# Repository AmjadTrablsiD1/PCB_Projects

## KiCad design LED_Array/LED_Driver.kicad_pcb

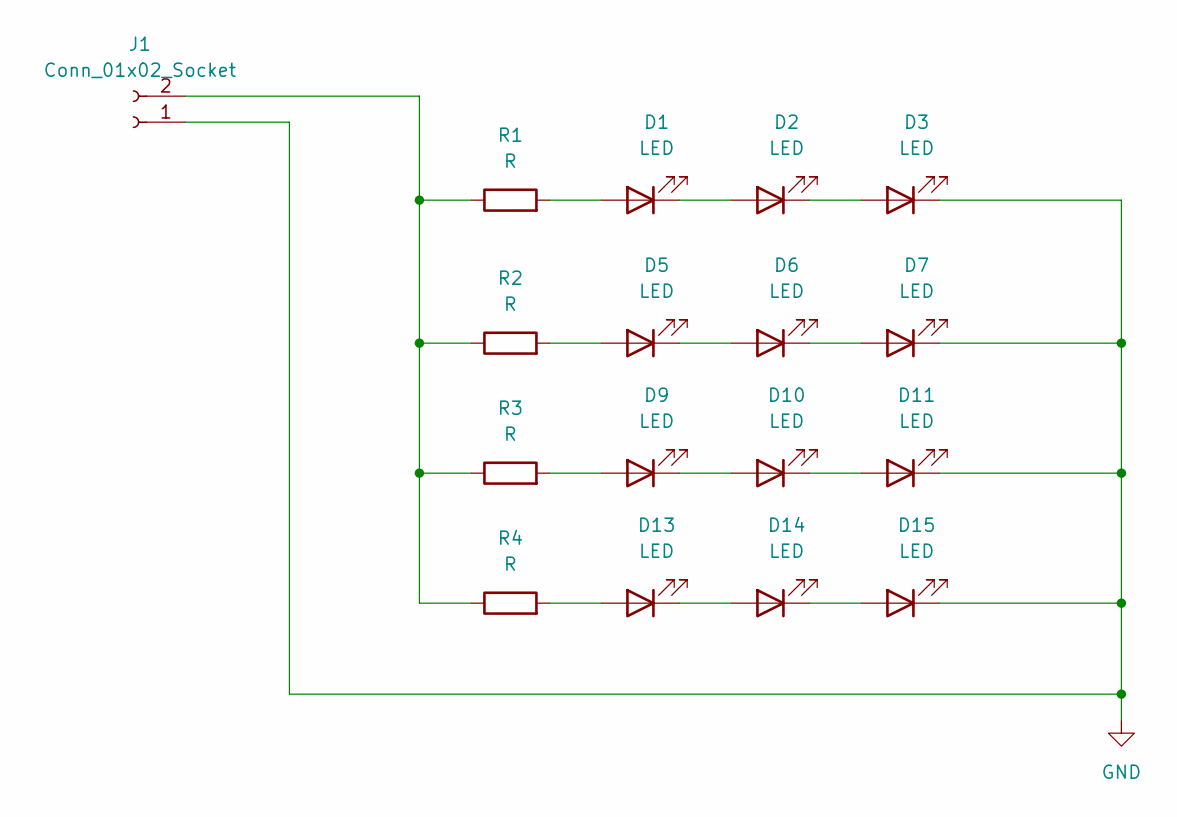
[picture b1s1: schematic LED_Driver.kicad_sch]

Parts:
D1, D2, D3, D5, D6, D7, D9, D10, D11, D13, D14, D15: LED; LED_1W_3W_R8
J1: Conn_01x02_Socket; PinSocket_1x02_P2.54mm_Vertical
R1, R2, R3, R4: R; R_1206_3216Metric_Pad1.30x1.75mm_HandSolder

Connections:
GND: D3.1 (K), D7.1 (K), D11.1 (K), D15.1 (K), J1.1
unnamed: D1.2 (A), R1.2
unnamed: D1.1 (K), D2.2 (A)
unnamed: D2.1 (K), D3.2 (A)
unnamed: D5.2 (A), R2.2
unnamed: D5.1 (K), D6.2 (A)
unnamed: D6.1 (K), D7.2 (A)
unnamed: D9.2 (A), R3.2
unnamed: D9.1 (K), D10.2 (A)
unnamed: D10.1 (K), D11.2 (A)
unnamed: D13.2 (A), R4.2
unnamed: D13.1 (K), D14.2 (A)
unnamed: D14.1 (K), D15.2 (A)
unnamed: J1.2, R1.1, R2.1, R3.1, R4.1

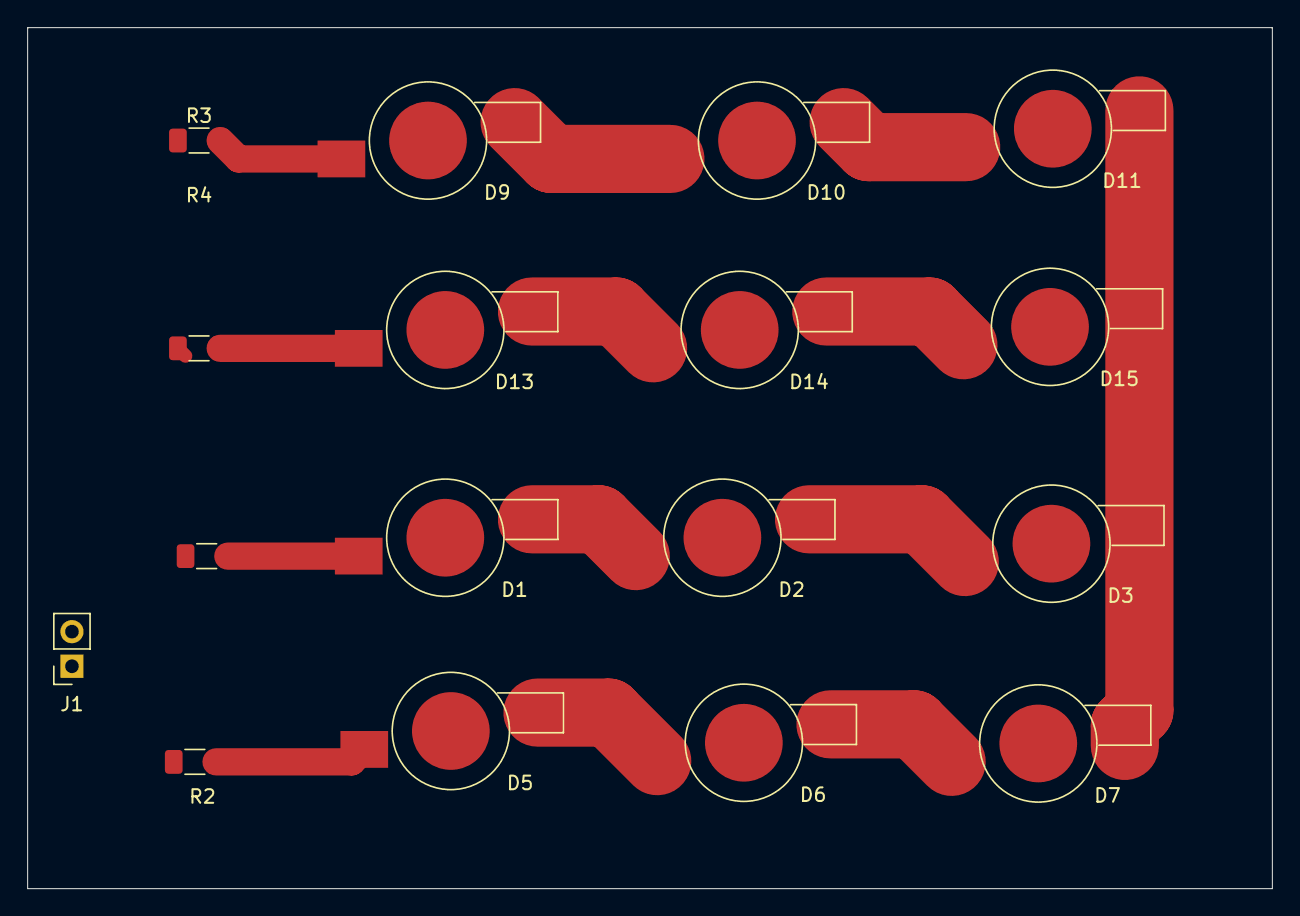
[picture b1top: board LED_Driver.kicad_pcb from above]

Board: 2 copper layers, 91.3 x 63.1 mm, 17 parts (0 on the bottom side), 14 nets.

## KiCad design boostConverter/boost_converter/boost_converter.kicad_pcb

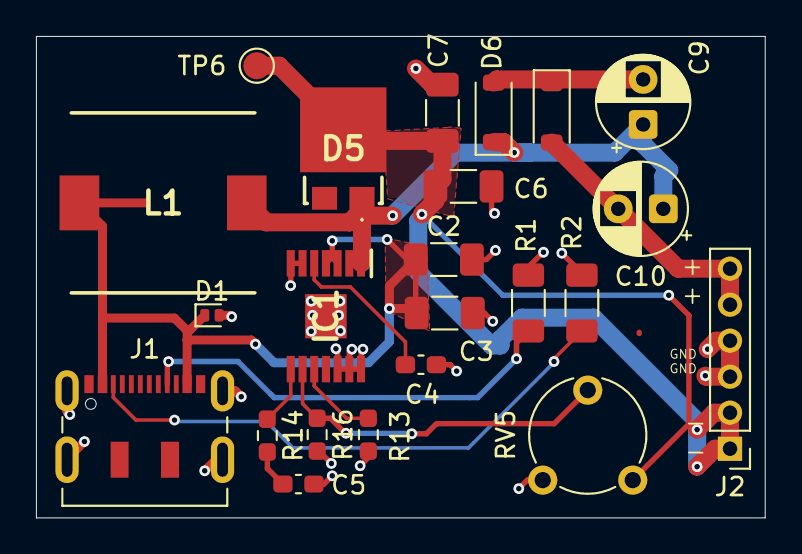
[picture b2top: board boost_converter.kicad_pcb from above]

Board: 4 copper layers, 40.5 x 26.7 mm, 23 parts (0 on the bottom side), 14 nets.

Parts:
C2, C3, C6, C7: 4u7; C_1206_3216Metric_Pad1.33x1.80mm_HandSolder
C4: 100n; C_0603_1608Metric_Pad1.08x0.95mm_HandSolder
C5: 1n; C_0603_1608Metric_Pad1.08x0.95mm_HandSolder
C9, C10: 100n; CP_Radial_D5.0mm_P2.50mm
D1: PESD5V0L1ULD; D_SOD-882D
D5: SS3P6L-E3_86A; SS3P6LE386A
D6, D7: MBR0520; D_SOD-123
IC1: TPS61175QPWPRQ1; SOP65P640X120-15N
J1: USB_C_Receptacle_PowerOnly_24P; USB_C_Receptacle_JAE_DX07S016JA1R1500
J2: Conn_01x06_Socket; PinHeader_1x06_P2.00mm_Vertical
L1: CDRH105RNP-220NC; INDPM102100X510N_Spule
R1, R2: 5k1; R_1206_3216Metric_Pad1.30x1.75mm_HandSolder
R13: 51k; R_0603_1608Metric_Pad0.98x0.95mm_HandSolder
R14: 1k; R_0603_1608Metric_Pad0.98x0.95mm_HandSolder
R16: 10K; R_0603_1608Metric_Pad0.98x0.95mm_HandSolder
RV5: R_Potentiometer; Potentiometer_Piher_PT-6-V_Vertical
TP6: TestPoint; TestPoint_Pad_D1.5mm

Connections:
5 V: C2.1, C3.1, D1.1 (K), IC1.3 (VIN), IC1.4 (EN), J1.A4 (VBUS), J1.A9 (VBUS), J1.B4 (VBUS), J1.B9 (VBUS), L1.1
25V: C6.1, C7.1, D5.3 (K), J2.1, J2.2, RV5.1, TP6.1
-25V: C10.2, D7.2 (A), J2.5, J2.6
GND: C2.2, C3.2, C4.2, C5.2, C6.2, C7.2, D1.2 (A), IC1.6 (SYNC), IC1.7 (AGND), IC1.12 (PGND_1), IC1.13 (PGND_2), IC1.14 (PGND_3), IC1.15 (EP), J2.3, J2.4, R1.2, R2.2, R13.2, R16.2, RV5.3
unnamed: C5.1, R14.2
unnamed: C9.1, C10.1, D5.1 (A_1), D6.1 (K), IC1.1 (SW_1), IC1.2 (SW_2), L1.2
unnamed: C9.2, D6.2 (A), D7.1 (K)
unnamed: IC1.8 (COMP), R14.1
unnamed: IC1.9 (FB), R16.1, RV5.2
unnamed: IC1.10 (FREQ), R13.1
unnamed: C4.1, IC1.5 (SS)
unnamed: J1.A5 (CC1), R2.1
unnamed: J1.B5 (CC2), R1.1
unnamed: J1.A1 (GND), J1.A12 (GND), J1.B1 (GND), J1.B12 (GND)

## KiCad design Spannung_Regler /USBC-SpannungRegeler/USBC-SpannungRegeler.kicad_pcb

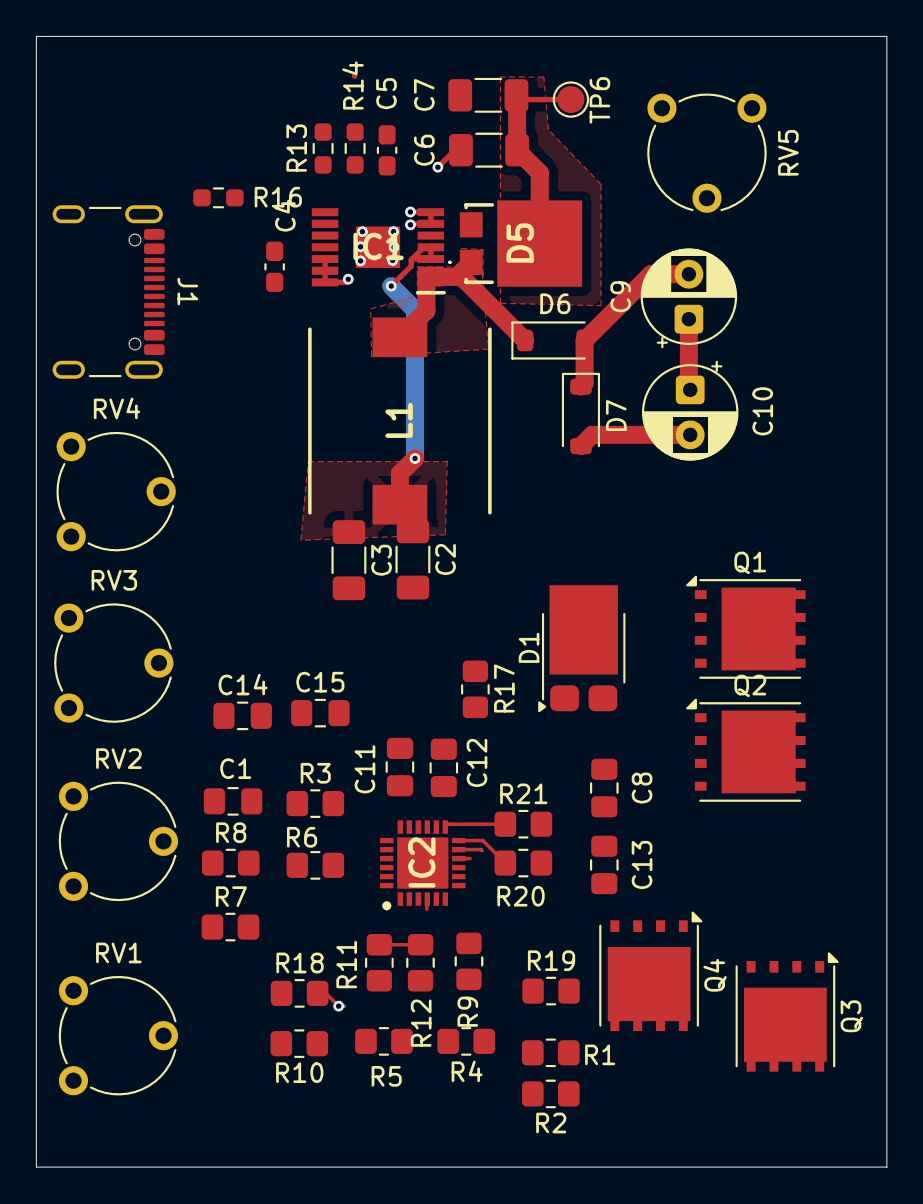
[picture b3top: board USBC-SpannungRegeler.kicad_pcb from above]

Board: 4 copper layers, 47.2 x 62.8 mm, 53 parts (0 on the bottom side), 31 nets.

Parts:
C1: 3u3; C_0805_2012Metric_Pad1.18x1.45mm_HandSolder
C2, C3, C6, C7: 4u7; C_1206_3216Metric_Pad1.33x1.80mm_HandSolder
C4: 100n; C_0603_1608Metric_Pad1.08x0.95mm_HandSolder
C5: 1n; C_0603_1608Metric_Pad1.08x0.95mm_HandSolder
C8, C11, C12, C13: 1u; C_0805_2012Metric_Pad1.18x1.45mm_HandSolder
C9, C10: 100n; CP_Radial_D5.0mm_P2.50mm
C14, C15: 0.1u; C_0805_2012Metric_Pad1.18x1.45mm_HandSolder
D1: PMEG030V050EPD; Nexperia_CFP15_SOT-1289
D5: SS3P6L-E3_86A; SS3P6LE386A
D6, D7: MBR0520; D_SOD-123
IC1: TPS61175QPWPRQ1; SOP65P640X120-15N
IC2: CYPD3177-24LQXQT
J1: USB4216-03-A; USB_C_Receptacle_GCT_USB4105-xx-A_16P_TopMnt_Horizontal
L1: CDRH105RNP-220NC; INDPM102100X510N_Spule
Q1, Q2, Q3, Q4: AON6411; AO_DFN-8-1EP_5.55x5.2mm_P1.27mm_EP4.12x4.6mm
R1, R2, R4, R5, R6, R7, R8, R11, R12, R18, R19: 1k; R_0805_2012Metric_Pad1.20x1.40mm_HandSolder
R3: 10k; R_0805_2012Metric_Pad1.20x1.40mm_HandSolder
R9: 4k7; R_0805_2012Metric_Pad1.20x1.40mm_HandSolder
R10, R17: 50k; R_0805_2012Metric_Pad1.20x1.40mm_HandSolder
R13: 51k; R_0603_1608Metric_Pad0.98x0.95mm_HandSolder
R14: 1k; R_0603_1608Metric_Pad0.98x0.95mm_HandSolder
R16: 10K; R_0603_1608Metric_Pad0.98x0.95mm_HandSolder
R20, R21: 2k2; R_0805_2012Metric_Pad1.20x1.40mm_HandSolder
RV1, RV2, RV3, RV4, RV5: R_Potentiometer; Potentiometer_Piher_PT-6-V_Vertical
TP6: TestPoint; TestPoint_Pad_D1.5mm

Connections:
5 V: C2.1, C3.1, IC1.3 (VIN), IC1.4 (EN), L1.1
25V: C6.1, C7.1, D5.3 (K), RV5.1, TP6.1
+3.3V: C12.1, C14.1, C15.1, IC2.23 (VDDD), R1.2, R4.2, R7.2, R9.1, R11.2, R20.2, R21.2, RV1.1, RV2.1, RV3.1, RV4.1
-25V: C10.2, D7.2 (A)
Coarse: IC2.5 (ISNK_COARSE), R1.1, R2.2, RV1.2
Fine: IC2.6 (ISNK_FINE), R4.1, R5.2, RV2.2
GND: C1.2, C2.2, C3.2, C4.2, C5.2, C6.2, C7.2, C11.2, C12.2, C14.2, C15.2, IC1.6 (SYNC), IC1.7 (AGND), IC1.12 (PGND_1), IC1.13 (PGND_2), IC1.14 (PGND_3), IC1.15 (EP), IC2.19 (GND_1), IC2.22 (GND_2), IC2.25 (EP), J1.A1 (GND_1), J1.B1 (GND_2), R2.1, R5.1, R8.1, R12.1, R13.2, R16.2, RV1.3, RV2.3, RV3.3, RV4.3, RV5.3
Max: IC2.2 (VBUS_MAX), R11.1, R12.2, RV3.2
Mini: IC2.1 (VBUS_MIN), R7.1, R8.2, RV4.2
unnamed: C5.1, R14.2
unnamed: D1.3 (K), Q1.1 (S), Q1.2 (S), Q1.3 (S), Q4.1 (S), Q4.2 (S), Q4.3 (S), R17.1
unnamed: C9.1, C10.1, D5.1 (A_1), D6.1 (K), IC1.1 (SW_1), IC1.2 (SW_2), L1.2
unnamed: C9.2, D6.2 (A), D7.1 (K)
unnamed: IC1.8 (COMP), R14.1
unnamed: IC1.9 (FB), R16.1, RV5.2
unnamed: IC1.10 (FREQ), R13.1
unnamed: C4.1, IC1.5 (SS)
unnamed: IC2.15 (CC1), J1.B5 (CC2)
unnamed: IC2.14 (CC2), J1.A5 (CC1)
unnamed: IC2.9 (FAULT), R19.1
unnamed: IC2.10 (FLIP), R9.2
unnamed: IC2.4 (SAFE_PWR_EN), R18.2
unnamed: IC2.3 (VBUS_FET_EN), R6.2
unnamed: C1.1, C8.1, IC2.18 (VBUS_IN), J1.A4 (VBUS_1), J1.B4 (VBUS_2), Q1.5 (D), Q2.5 (D), R3.1, R10.1
unnamed: C11.1, IC2.24 (VCCD)
unnamed: C8.2, C13.2, D1.1 (A), D1.2 (A), Q1.4 (G), Q4.4 (G), R3.2, R6.1, R17.2
unnamed: Q2.4 (G), Q3.4 (G), R10.2, R18.1
unnamed: Q2.1 (S), Q2.2 (S), Q2.3 (S), Q3.1 (S), Q3.2 (S), Q3.3 (S)
SCL: IC2.13 (HPI_SCL), R21.1
SDA: IC2.12 (HPI_SDA), R20.1
V_out: C13.1, IC2.11 (VDC_OUT), Q4.5 (D)

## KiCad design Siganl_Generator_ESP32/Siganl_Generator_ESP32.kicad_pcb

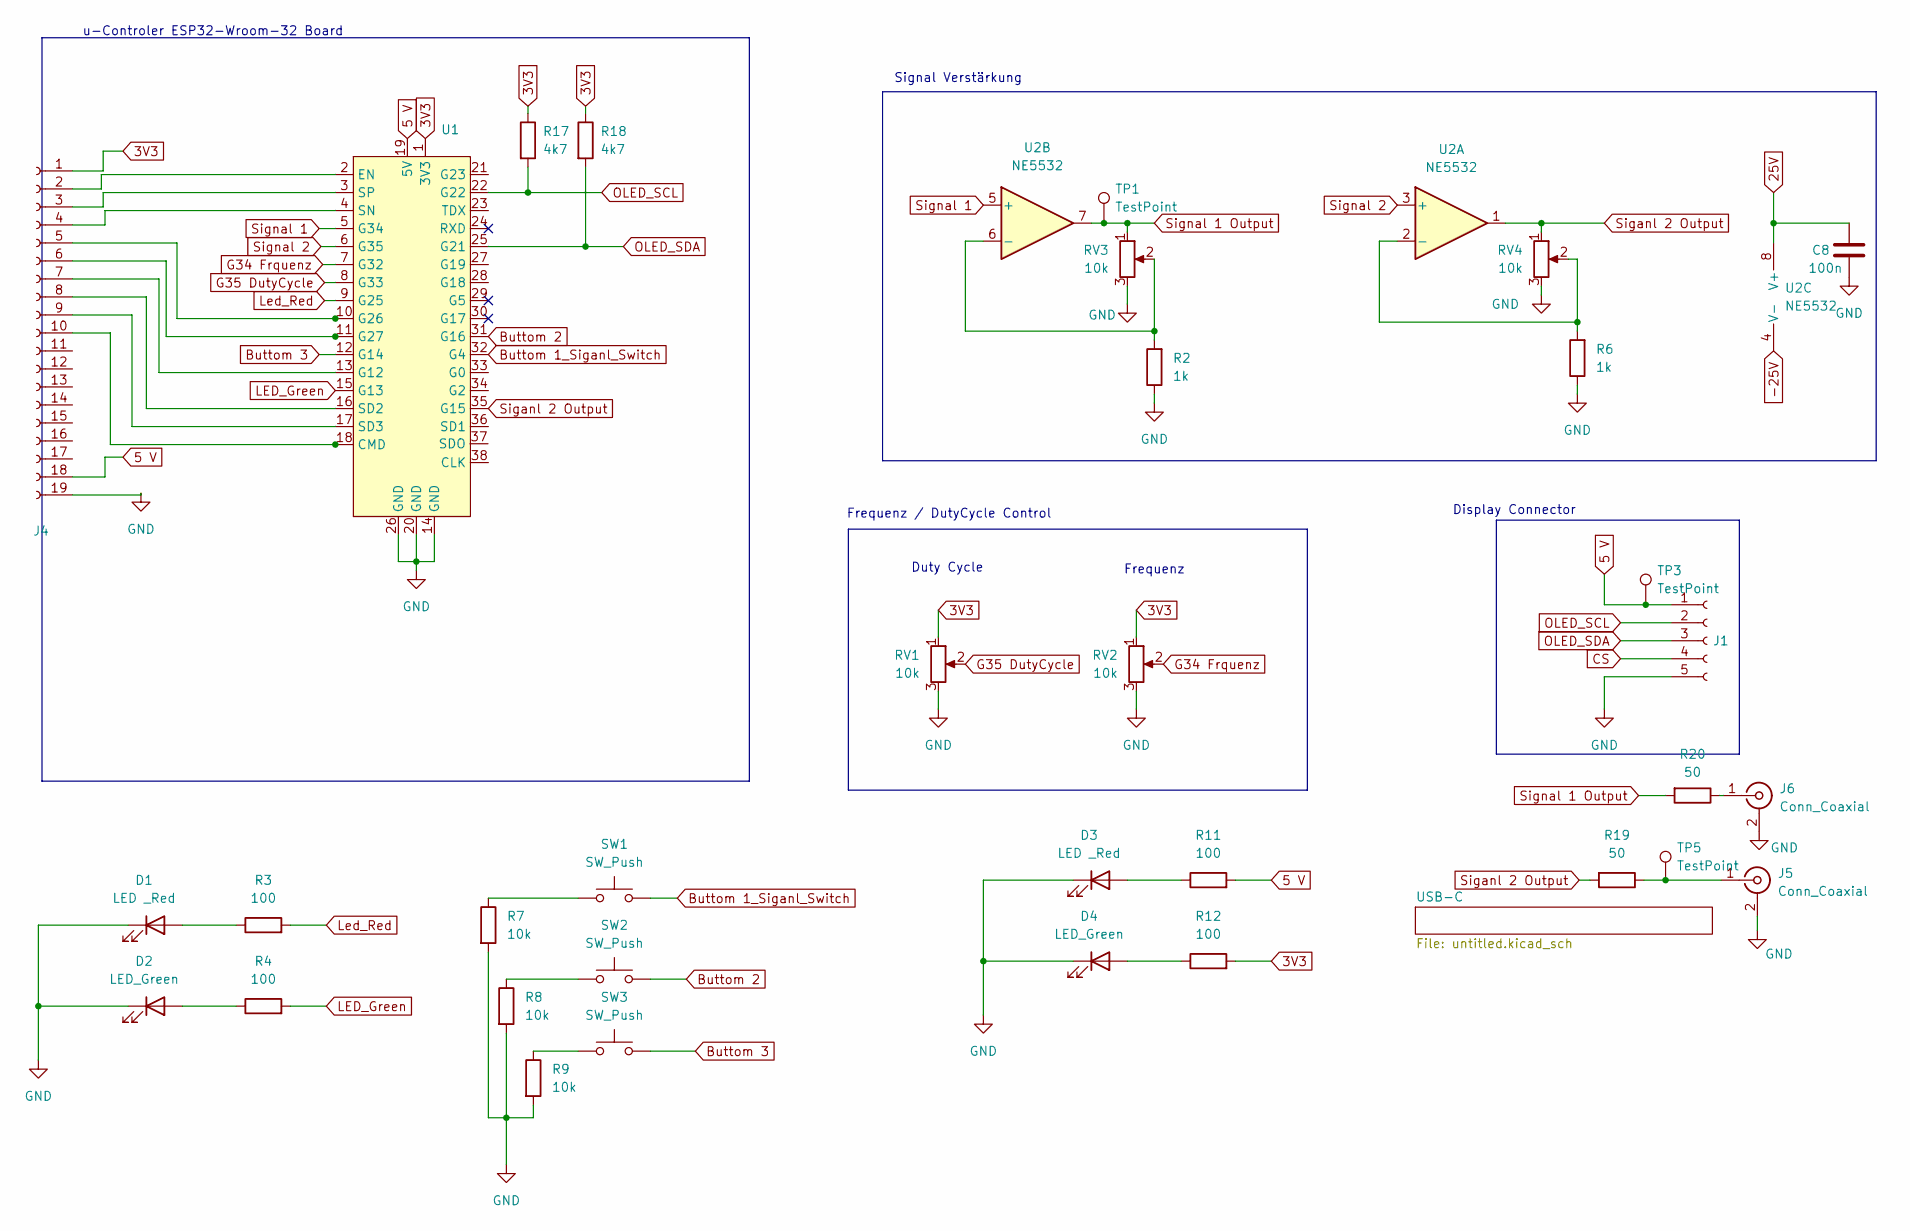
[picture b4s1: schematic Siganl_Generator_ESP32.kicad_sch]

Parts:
C8: 100n; C_0603_1608Metric_Pad1.08x0.95mm_HandSolder
D1, D3: LED _Red; D_1206_3216Metric
D2, D4: LED_Green; D_1206_3216Metric
J1: Conn_01x05_Socket; PinSocket_1x05_P2.54mm_Vertical
J4: Conn_01x19_Socket; PinSocket_1x19_P2.54mm_Vertical
J5, J6: Conn_Coaxial; SMA_Amphenol_132289_EdgeMount
R2, R6: 1k; R_0603_1608Metric_Pad0.98x0.95mm_HandSolder
R3, R4, R11, R12: 100; R_0603_1608Metric_Pad0.98x0.95mm_HandSolder
R7, R8, R9: 10k; R_0603_1608Metric_Pad0.98x0.95mm_HandSolder
R17, R18: 4k7; R_0603_1608Metric_Pad0.98x0.95mm_HandSolder
R19, R20: 50; R_0603_1608Metric_Pad0.98x0.95mm_HandSolder
RV1, RV2, RV3, RV4: 10k; Potentiometer_Alps_RK163_Single_Horizontal
SW1, SW2, SW3: SW_Push; SW_PUSH-12mm
TP1, TP3: TestPoint; TestPoint_Pad_D1.0mm
TP5: TestPoint; TestPoint_Pad_D1.5mm
U1: ESP_32_socket
U2: NE5532; DIP-8_W7.62mm

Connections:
3V3: J4.1, R12.2, R17.1, R18.1, RV1.1, RV2.1, U1.1 (3V3)
5 V: J1.1, J4.18, R11.2, TP3.1, U1.19 (5V); also elsewhere on the board
25V: C8.1, U2.8 (V+); also elsewhere on the board
-25V: U2.4 (V-); also elsewhere on the board
Buttom 1_Siganl_Switch: SW1.2, U1.32 (G4)
Buttom 2: SW2.2, U1.31 (G16)
Buttom 3: SW3.2, U1.12 (G14)
CS: J1.4
G34 Frquenz: RV2.2, U1.7 (G32)
G35 DutyCycle: RV1.2, U1.8 (G33)
GND: C8.2, D1.1 (K), D2.1 (K), D3.1 (K), D4.1 (K), J1.5, J4.19, J5.2 (Ext), J6.2 (Ext), R2.1, R6.1, R7.2, R8.2, R9.2, RV1.3, RV2.3, RV3.3, RV4.3, U1.14 (GND), U1.20 (GND), U1.26 (GND); also elsewhere on the board
LED_Green: R4.2, U1.15 (G13)
Led_Red: R3.2, U1.9 (G25)
unnamed: D1.2 (A), R3.1
unnamed: D2.2 (A), R4.1
unnamed: D3.2 (A), R11.1
unnamed: D4.2 (A), R12.1
unnamed: J4.2, U1.2 (EN)
unnamed: J4.3, U1.3 (SP)
unnamed: J4.4, U1.4 (SN)
unnamed: J4.5, U1.10 (G26)
unnamed: J4.6, U1.11 (G27)
unnamed: J4.7, U1.13 (G12)
unnamed: J4.8, U1.16 (SD2)
unnamed: J4.9, U1.17 (SD3)
unnamed: J4.10, U1.18 (CMD)
unnamed: J5.1 (In), R19.1, TP5.1
unnamed: J6.1 (In), R20.1
unnamed: R7.1, SW1.1
unnamed: R8.1, SW2.1
unnamed: R9.1, SW3.1
unnamed: R6.2, RV4.2, U2.2 (-)
unnamed: R2.2, RV3.2, U2.6 (-)
OLED_SCL: J1.2, R17.2, U1.22 (G22)
OLED_SDA: J1.3, R18.2, U1.25 (G21)
Siganl 2 Output: R19.2, RV4.1, U1.35 (G15), U2.1
Signal 1: U1.5 (G34), U2.5 (+)
Signal 1 Output: R20.2, RV3.1, TP1.1, U2.7
Signal 2: U1.6 (G35), U2.3 (+)

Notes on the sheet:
u-Controler ESP32-Wroom-32 Board
Signal Verstärkung
Frequenz / DutyCycle Control
Display Connector
Frequenz
Duty Cycle

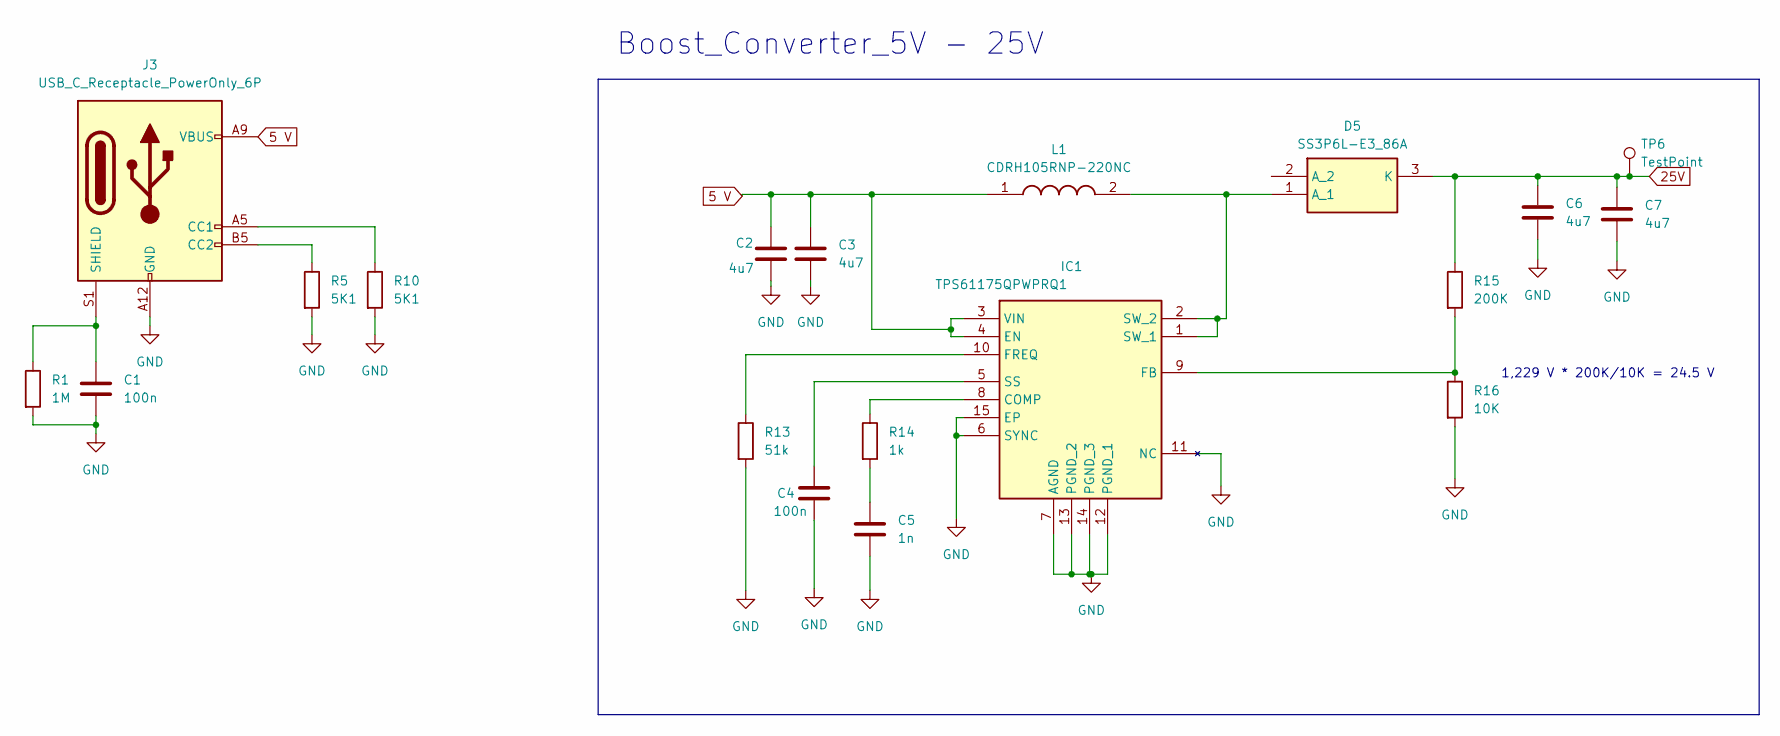
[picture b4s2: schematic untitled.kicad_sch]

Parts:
C1: 100n; C_1206_3216Metric
C2, C3, C6, C7: 4u7; C_1206_3216Metric_Pad1.33x1.80mm_HandSolder
C4: 100n; C_0603_1608Metric_Pad1.08x0.95mm_HandSolder
C5: 1n; C_0603_1608Metric_Pad1.08x0.95mm_HandSolder
D5: SS3P6L-E3_86A; SS3P6LE386A; Manufacturer_Part_Number SS3P6L-E3/86A
IC1: TPS61175QPWPRQ1; SOP65P640X120-15N; Mouser Part Number 595-TPS61175QPWPRQ1
J3: USB_C_Receptacle_PowerOnly_6P; USB_C_Receptacle_GCT_USB4125-xx-x-0190_6P_TopMnt_Horizontal
L1: CDRH105RNP-220NC; INDPM102100X510N_Spule; Mouser Part Number 851-CDRH105RNP-220NC
R1: 1M; R_1206_3216Metric
R5, R10: 5K1; R_0603_1608Metric_Pad0.98x0.95mm_HandSolder
R13: 51k; R_0603_1608Metric_Pad0.98x0.95mm_HandSolder
R14: 1k; R_0603_1608Metric_Pad0.98x0.95mm_HandSolder
R15: 200K; R_0603_1608Metric_Pad0.98x0.95mm_HandSolder
R16: 10K; R_0603_1608Metric_Pad0.98x0.95mm_HandSolder
TP6: TestPoint; TestPoint_Pad_D1.5mm

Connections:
5 V: C2.1, C3.1, IC1.3 (VIN), IC1.4 (EN), J3.A9 (VBUS), J3.B9 (VBUS), L1.1; also elsewhere on the board
25V: C6.1, C7.1, D5.3 (K), R15.1, TP6.1; also elsewhere on the board
GND: C1.2, C2.2, C3.2, C4.2, C5.2, C6.2, C7.2, IC1.6 (SYNC), IC1.7 (AGND), IC1.11 (NC), IC1.12 (PGND_1), IC1.13 (PGND_2), IC1.14 (PGND_3), IC1.15 (EP), J3.A12 (GND), J3.B12 (GND), R1.2, R5.2, R10.2, R13.2, R16.2; also elsewhere on the board
unnamed: C5.1, R14.2
unnamed 18: D5.1 (A_1), IC1.1 (SW_1), IC1.2 (SW_2), L1.2; also elsewhere on the board
unnamed: IC1.8 (COMP), R14.1
unnamed: IC1.9 (FB), R15.2, R16.1
unnamed: IC1.10 (FREQ), R13.1
unnamed: C4.1, IC1.5 (SS)
unnamed: J3.A5 (CC1), R10.1
unnamed: J3.B5 (CC2), R5.1
unnamed: C1.1, J3.S1 (SHIELD), R1.1

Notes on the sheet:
1,229 V * 200K/10K = 24.5 V
Boost_Converter_5V - 25V

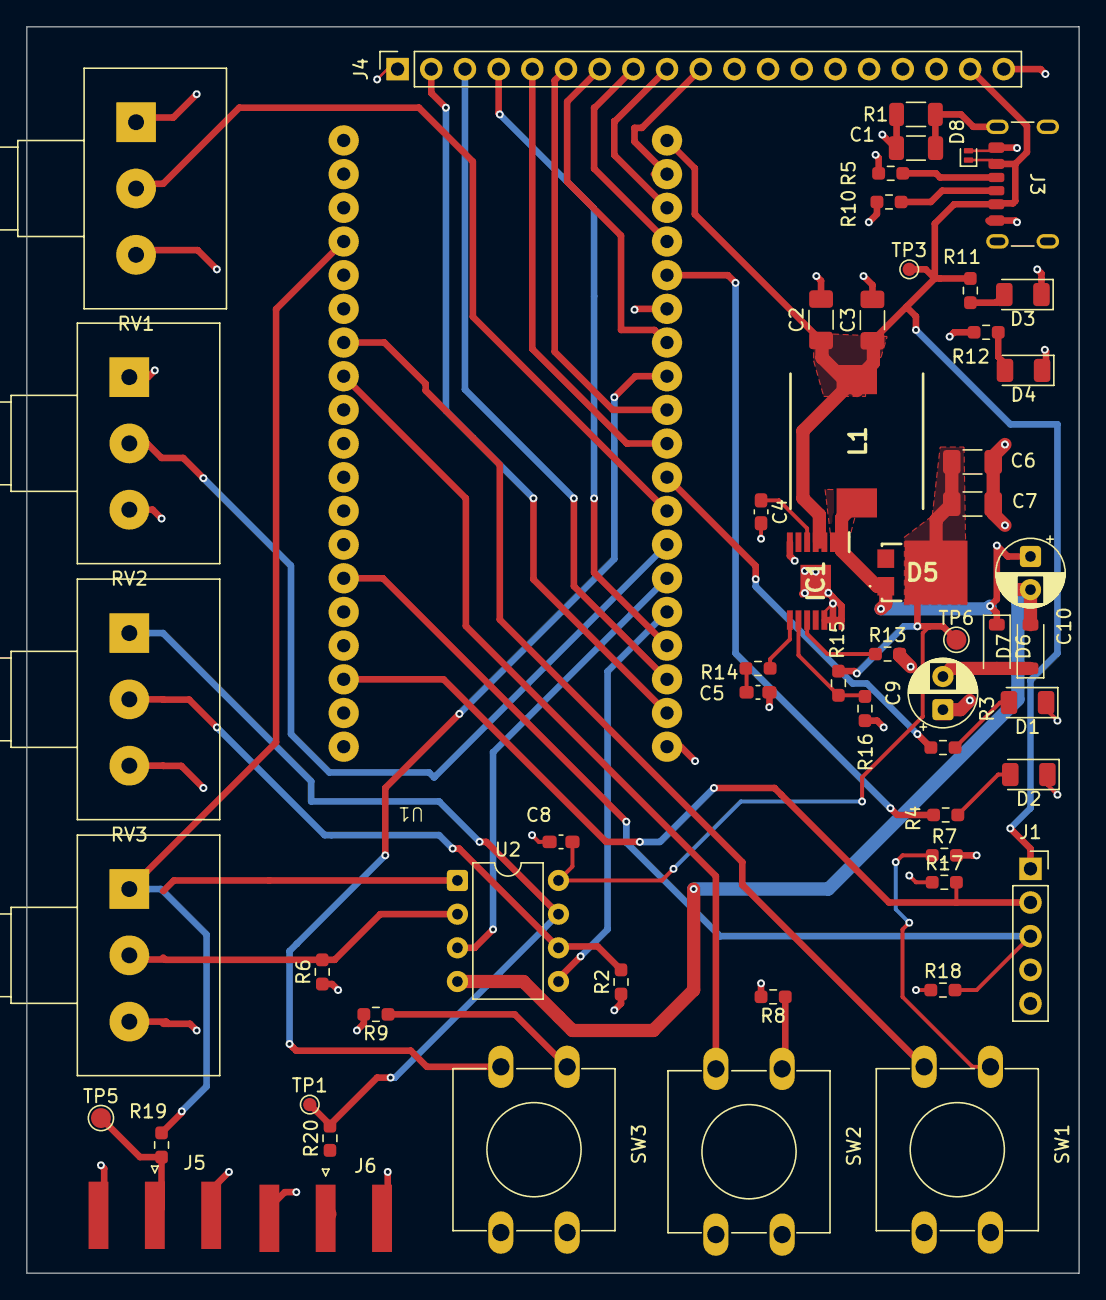
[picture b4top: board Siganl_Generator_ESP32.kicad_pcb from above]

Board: 4 copper layers, 79.4 x 94.0 mm, 58 parts (0 on the bottom side), 48 nets.

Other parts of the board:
C9, C10: 100n; CP_Radial_D5.0mm_P2.50mm
D6, D7: MBR0520; D_SOD-123
D8: PESD5V0L1UL; D_SOD-882

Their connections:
5 V: D8.1 (K); also elsewhere on the board
-25V: C10.2, D7.2 (A); also elsewhere on the board
GND: D8.2 (A); also elsewhere on the board
unnamed 18: C9.1, C10.1, D6.1 (K); also elsewhere on the board
unnamed: C9.2, D6.2 (A), D7.1 (K)

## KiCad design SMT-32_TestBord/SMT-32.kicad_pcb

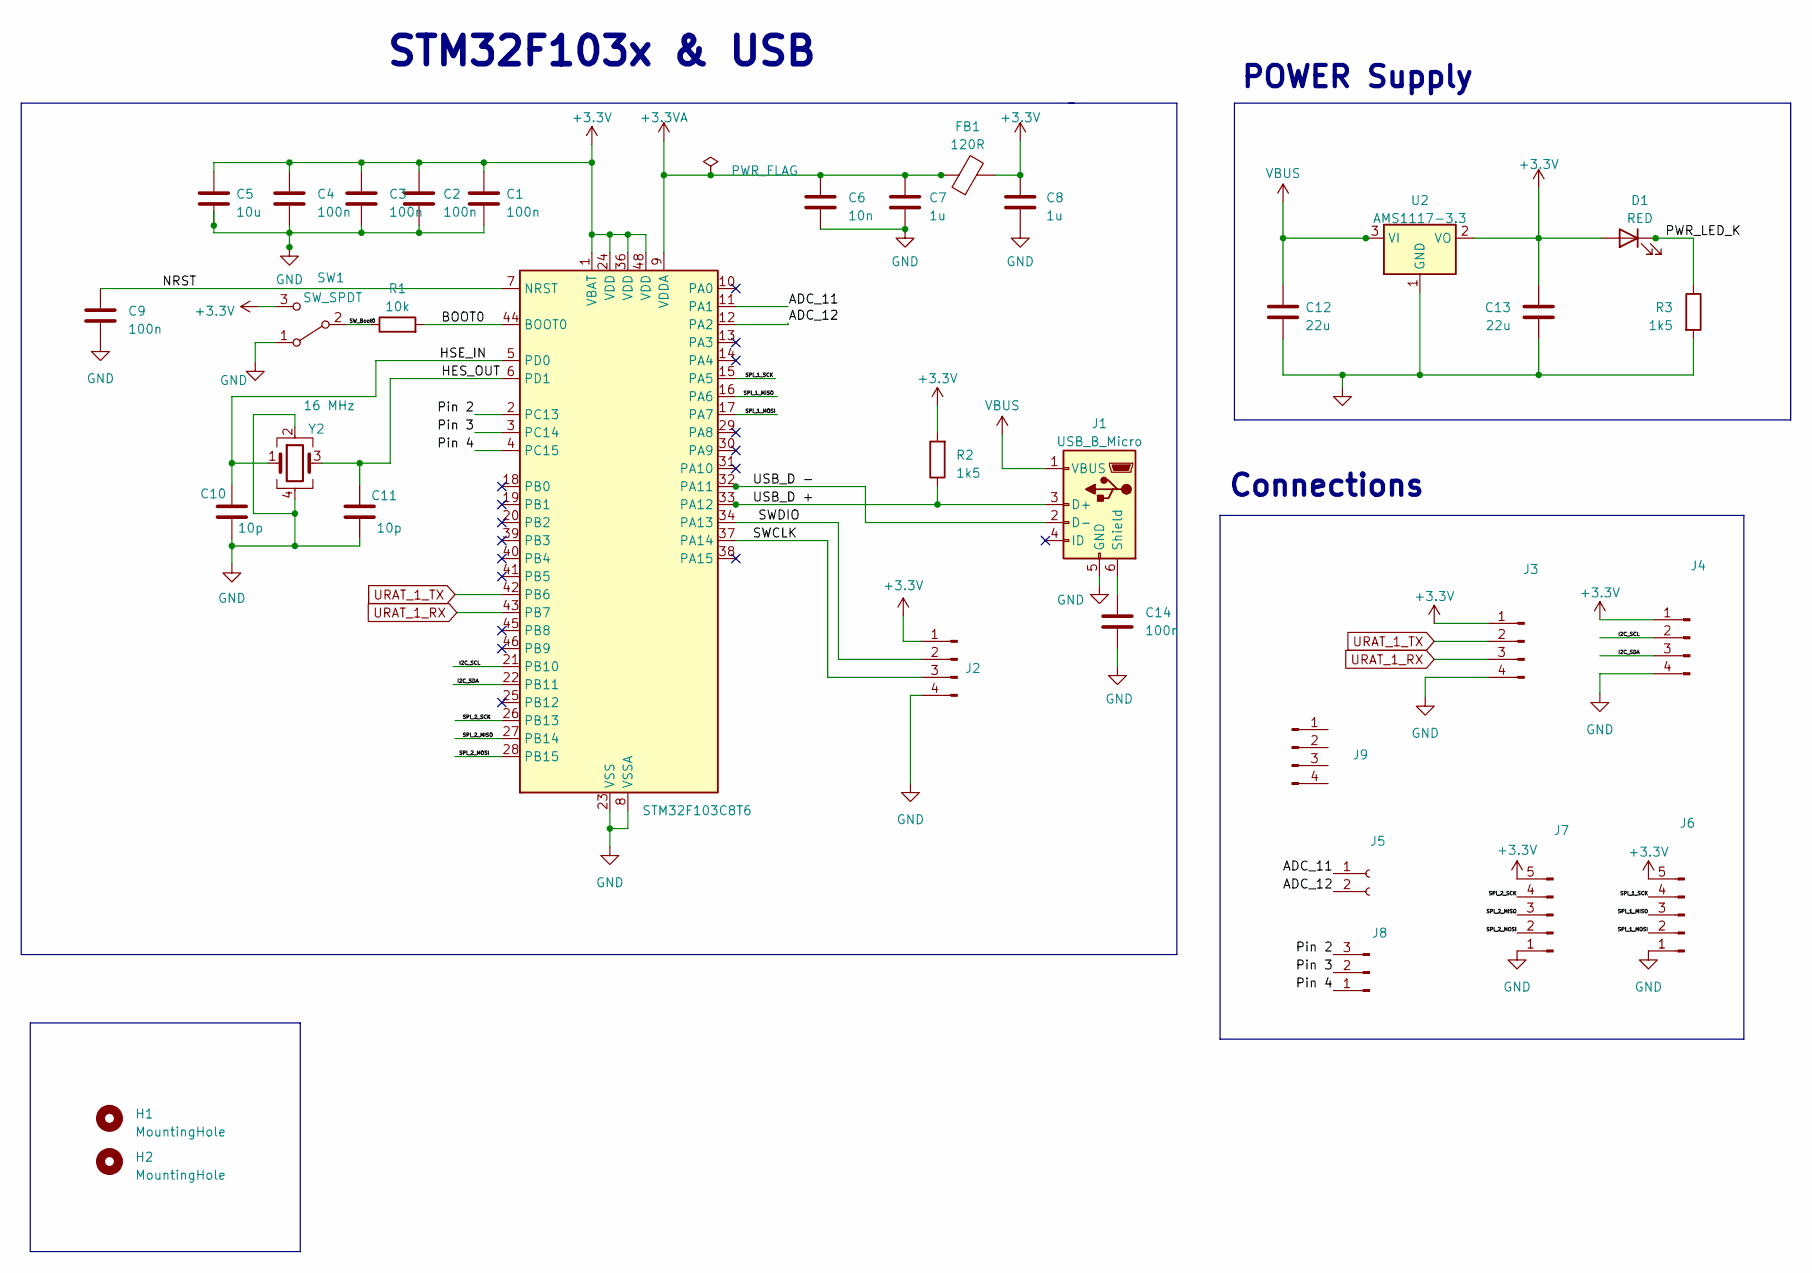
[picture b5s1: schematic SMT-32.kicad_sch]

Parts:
C1, C2, C3, C4, C9, C14: 100n; C_0402_1005Metric
C5: 10u; C_0603_1608Metric
C6: 10n; C_0402_1005Metric
C7, C8: 1u; C_0402_1005Metric
C10, C11: 10p; C_0402_1005Metric
C12, C13: 22u; C_0805_2012Metric
D1: RED; LED_0603_1608Metric
FB1: 120R; L_0603_1608Metric
H1, H2: MountingHole; MountingHole_2.1mm
J1: USB_B_Micro; USB_Micro-B_Wuerth_629105150521
J2, J3, J4: Conn_01x04_Pin; PinHeader_1x04_P2.54mm_Vertical
J5: Conn_01x02_Socket; PinSocket_1x02_P2.54mm_Vertical
J6, J7: Conn_01x05_Pin; PinHeader_1x05_P2.54mm_Vertical
J8: Conn_01x03_Pin; PinHeader_1x03_P2.54mm_Vertical
J9: Conn_01x04_Pin
R1: 10k; R_0402_1005Metric
R2, R3: 1k5; R_0402_1005Metric
SW1: SW_SPDT; SW_SPDT_PCM12
U1: STM32F103C8T6; LQFP-48_7x7mm_P0.5mm
U2: AMS1117-3.3; SOT-223-3_TabPin2
Y2: 16 MHz; Crystal_SMD_3225-4Pin_3.2x2.5mm

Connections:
+3.3V: C1.1, C2.1, C3.1, C4.1, C5.1, C8.1, C13.1, D1.2 (A), FB1.2, J2.1, J3.1, J4.1, J6.5, J7.5, R2.2, SW1.3 (C), U1.1 (VBAT), U1.24 (VDD), U1.36 (VDD), U1.48 (VDD), U2.2 (VO)
+3.3VA: C6.1, C7.1, FB1.1, U1.9 (VDDA)
/ADC_11: J5.1, U1.11 (PA1)
/ADC_12: J5.2, U1.12 (PA2)
/BOOT0: R1.2, U1.44 (BOOT0)
/HES_OUT: C11.1, U1.6 (PD1), Y2.3
/HSE_IN: C10.1, U1.5 (PD0), Y2.1
/I2C_SCL: J4.2, U1.21 (PB10)
/I2C_SDA: J4.3, U1.22 (PB11)
/NRST: C9.1, U1.7 (NRST)
/PWR_LED_K: D1.1 (K), R3.1
/Pin 2: J8.3, U1.2 (PC13)
/Pin 3: J8.2, U1.3 (PC14)
/Pin 4: J8.1, U1.4 (PC15)
/SPI_1_MISO: J6.3, U1.16 (PA6)
/SPI_1_MOSI: J6.2, U1.17 (PA7)
/SPI_1_SCK: J6.4, U1.15 (PA5)
/SPI_2_MISO: J7.3, U1.27 (PB14)
/SPI_2_MOSI: J7.2, U1.28 (PB15)
/SPI_2_SCK: J7.4, U1.26 (PB13)
/SWCLK: J2.3, U1.37 (PA14)
/SWDIO: J2.2, U1.34 (PA13)
/SW_Boot0: R1.1, SW1.2 (B)
/USB_D +: J1.3 (D+), R2.1, U1.33 (PA12)
/USB_D -: J1.2 (D-), U1.32 (PA11)
GND: C1.2, C2.2, C3.2, C4.2, C5.2, C6.2, C7.2, C8.2, C9.2, C10.2, C11.2, C12.2, C13.2, C14.2, J1.5 (GND), J2.4, J3.4, J4.4, J6.1, J7.1, R3.2, SW1.1 (A), U1.8 (VSSA), U1.23 (VSS), U1.35 (VSS), U1.47 (VSS), U2.1 (GND), Y2.2, Y2.4
unnamed: C14.1, J1.6 (Shield)
URAT_1_RX: J3.3, U1.43 (PB7)
URAT_1_TX: J3.2, U1.42 (PB6)
VBUS: C12.1, J1.1 (VBUS), U2.3 (VI)

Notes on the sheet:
POWER Supply
Connections
STM32F103x & USB

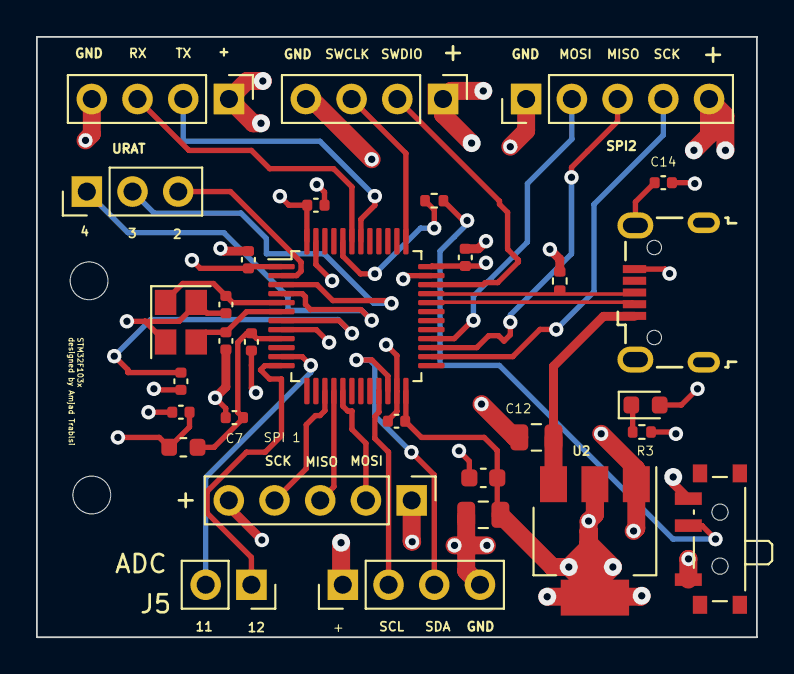
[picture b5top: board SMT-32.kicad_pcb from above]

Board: 4 copper layers, 40.0 x 33.4 mm, 33 parts (0 on the bottom side), 30 nets.

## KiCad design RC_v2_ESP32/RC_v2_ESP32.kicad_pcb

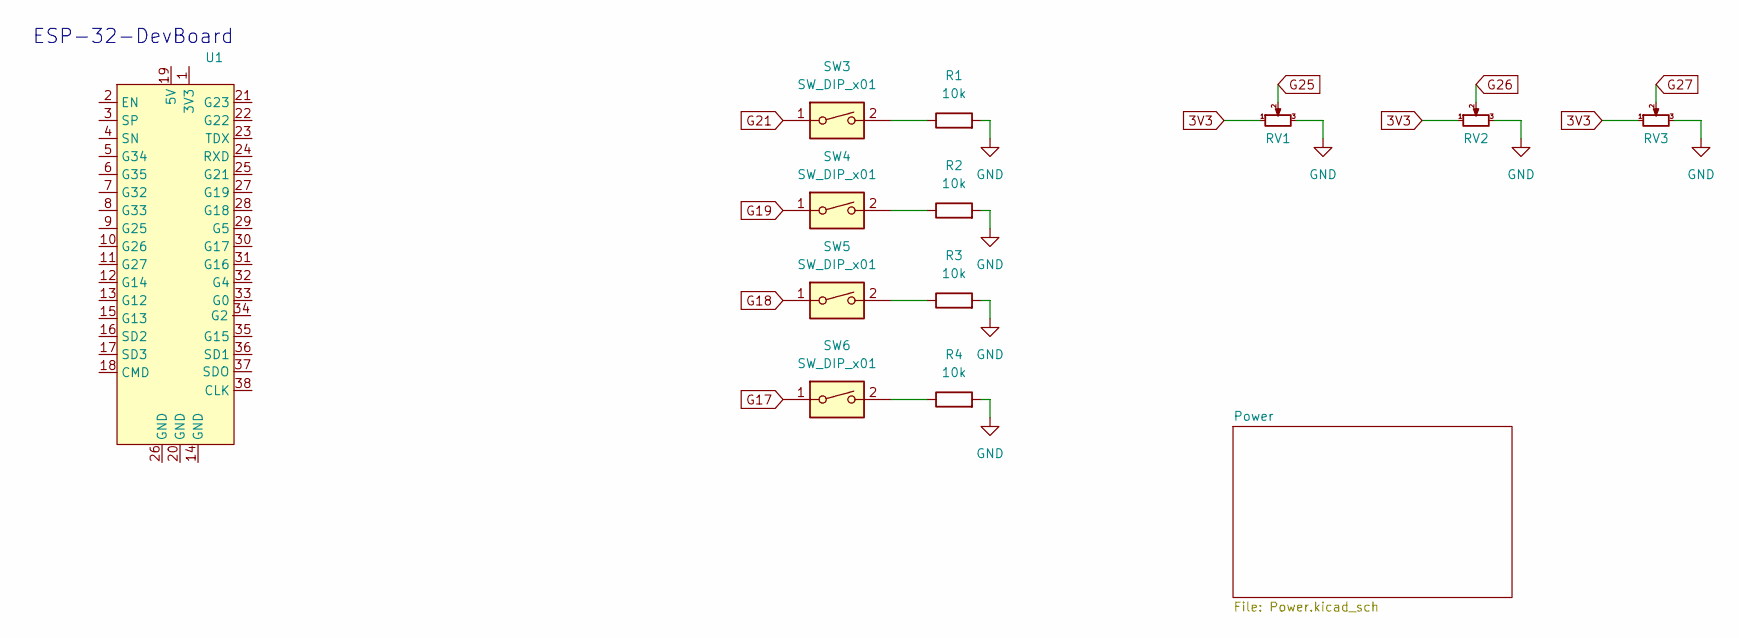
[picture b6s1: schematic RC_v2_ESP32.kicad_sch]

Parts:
R1, R2, R3, R4: 10k; R_1206_3216Metric
RV1, RV2, RV3: R_Potentiometer_Small; Potentiometer_Alps_RK09K_Single_Vertical
SW3, SW4, SW5, SW6: SW_DIP_x01; SW_Push_1P1T_XKB_TS-1187A
U1: ESP_32_socket

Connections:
3V3: RV1.1, RV2.1, RV3.1
G17: SW6.1
G18: SW5.1
G19: SW4.1
G21: SW3.1
G25: RV1.2
G26: RV2.2
G27: RV3.2
GND: R1.2, R2.2, R3.2, R4.2, RV1.3, RV2.3, RV3.3
unnamed: R1.1, SW3.2
unnamed: R2.1, SW4.2
unnamed: R3.1, SW5.2
unnamed: R4.1, SW6.2

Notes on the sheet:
ESP-32-DevBoard

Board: 2 copper layers, 12 parts (0 on the bottom side), 6 nets, no tracks yet.

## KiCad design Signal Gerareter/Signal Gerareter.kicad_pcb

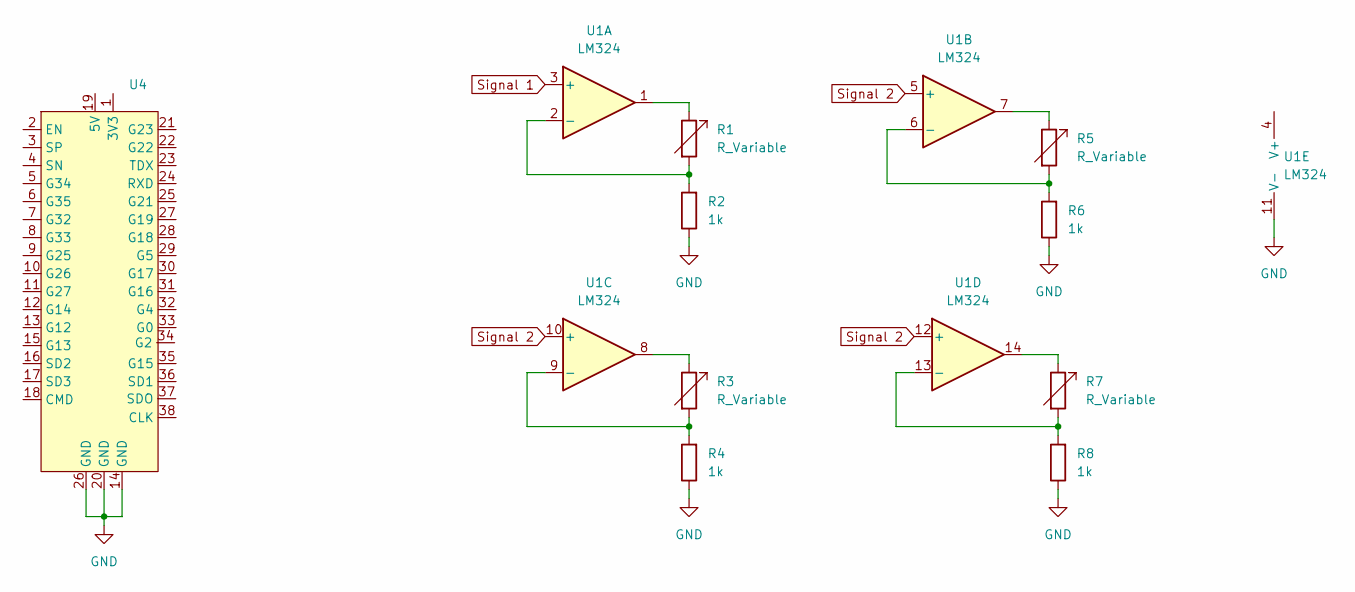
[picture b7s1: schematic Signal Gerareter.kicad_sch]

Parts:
R1, R3, R5, R7: R_Variable; Potentiometer_Alps_RK163_Single_Horizontal
R2, R4: 1k; R_1206_3216Metric
R6, R8: 1k; R_1210_3225Metric
U1: LM324; LM324_4
U4: ESP_32_socket

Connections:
GND: R2.1, R4.1, R6.1, R8.1, U1.11 (V-), U4.14 (GND), U4.20 (GND), U4.26 (GND)
unnamed: R1.1, U1.1
unnamed: R3.1, U1.8
unnamed: R5.1, U1.7
unnamed: R7.1, U1.14
unnamed: R1.2, R2.2, U1.2 (-)
unnamed: R5.2, R6.2, U1.6 (-)
unnamed: R3.2, R4.2, U1.9 (-)
unnamed: R7.2, R8.2, U1.13 (-)
Signal 1: U1.3 (+)
Signal 2: U1.5 (+), U1.10 (+), U1.12 (+)

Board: 2 copper layers, 10 parts (0 on the bottom side), 10 nets, no tracks yet.
